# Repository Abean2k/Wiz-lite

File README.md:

# WizLite

A small, 2 player capable, ch552 based, game console with a 14x9 rgb led screen. 

## Design and Inspo:
I while back, I ordered some parts from LCSC, and as a part of that order I got a discounted CH552g chip. So, I wanted to find something cool and fun to do with it. My "solution", make a 'simple' two player game controller. 

In the process of building this, I made a number of decisions that made what was supposed to be a simple game controller into... an overengineered, ambitious project. For example, a simple OLED screen would have worked but did I do that, no. I wanted to make a small matrix of LEDS, which then became a matrix of rgb LEDS, which then finally became a tiny (807 size) 14x9 LED matrix. Additionally, the form factor of this whole project is VERY small (only around 75x50mm), making it even more interesting ;) 

## PCB:
For this project I made a two-layer PCB on Kicad, I limited myself to two layers in order to reduce the cost of the pcb manufacturing and to make it simpler. The pcb is lightly bigger than 75x50mm, and is designed with the LED matrix screen in the middle, the buttons on the top and bottom, Ch552 + passives to the right, and USB + passives to left. 

On the pcb, I added some text to demarcate the player one and player two sides, and I also added some pcb art to the front and back for *aesthetics*. 

### Schematic: 

### PCB Layout:

### Assembly/Ordering: 
The LED pads used on the pcb are technically over the "fine pitch" threshold of JLCPCB, and as such could be ordered with HASL. However, I recommend getting either OSP or ENIG as their pads are much flatter. When ordering, I would also make sure to order a stencil, as applying solder paste to the small led pads is very hard to do without applying excess solder. While soldering/reflowing, also make sure to not heat the leds too much (max 20 seconds at reflow tempurature).

You could also get the pcb assembled through something like JLCPCB PCBA service, however I chose not to for price saving reasons. 

## Firmware:
This project has the main firmware written in C, for the Arduino IDE, using the ch55xdunio library. Using C was new for me, but it was very similar to C++, and I was able to get a hang of it decently quickly. The basic idea is that the firmware drives the 9x14 RGB LED matrix, reads the user buttons, and executes game instructions. The firmware was (in my opinion) the hardest part of this project, but it also what I am most proud of. Anyway, here is the full breakdown of the code and other details about it.

#### Games (only one for now):
- Snake (single player)
- More TBD

Hold Player 1 LEFT + RIGHT for 2 seconds to leave a game and return to the menu.

#### How it works (like very high level) :
- **Menu:** A carousel of game cover pictures. LEFT/RIGHT pans, UP starts the selected game.
- **Screen:** screenUpdate(x, y, r, g, b) sets a pixel with (0,0) at the top left. It handles the split display, the zigzag LED wiring and a brightness limit so USB power limits aren't excided, and stores the result directly in the LED buffer. screenShow() sends that to the LEDs to acutally turn it on.
- **Pictures:** Each picture (like on the game cover carousel) has its own list of colors plus 14 rows of 9 characters. Use PictureMaker.html to draw one or import it from a Figma screenshot, and it writes the code for you. **NOTE:** This part (and only this part) of the code was made fully using AI, it looks vide coded, and that is because it is. Please understand if there are small bugs in it.
- **Text:** I added a 3x5 font (A-Z, 0-9) that can be called separately or with micro:bit style scrolling for longer texts.

#### Files:
| File | Purpose |
|---|---|
| `WizGameLite.ino` | Game menu and game list |
| `WizBase.c / .h` | Screen, buttons, text, shared pictures |
| `Snake.c / .h` | Snake game and its cover picture |
| `PictureMaker.html` | Tool for making pictures (opens in a browser, make sure javascript is enabled) |

#### PictureMaker:

#### Adding a game:
See the "HOW TO ADD A GAME" comment in `WizGameLite.ino`.

#### AI Usage: 
The code for the actual controller was fully coded by me (with only limited debug and learning help from AI). However, the online picture maker was fully vibe code, and it was also the first time I ever have vibe coded :)

## BOM: 
| Part | Designators | Quantity | Retailer | Total Price | Link |
|------|-------------|----------|----------|-------------|------|
| XL-0807RGBC-2812B-S (WS2812B-style addressable RGB LED, 2.0x1.8mm) `C41413181` | U2–U127 | 126x5 (640 ordered) | LCSC | $13.38 | [LCSC](https://www.lcsc.com/product-detail/C41413181.html) |
| 47uF ±10% 16V Ceramic Capacitor, 1210 (CS3225X7R476K160NRL) `C5440143` | C3, C4 | 2x5 | LCSC | $2.23 | [LCSC](https://www.lcsc.com/product-detail/C5440143.html) |
| 10kΩ ±1% 0805 Resistor (0805W8F1002T5E) `C17414` | R1–R4, R7–R11 | 9x5 (100 MOQ) | LCSC | $0.34 | [LCSC](https://www.lcsc.com/product-detail/C17414.html) |
| 100n Capacitor, 0805 | C1, C2 | 2x5 | Already have | $0.00 | [LCSC](https://www.lcsc.com/product-detail/C1711.html) |
| 330Ω Resistor, 0805 | R12, R13 | 2x5 | Already have | $0.00 | [LCSC](https://www.lcsc.com/product-detail/C17630.html) |
| 5.1kΩ Resistor, 0805 | R5, R6 | 2x5 | Already have | $0.00 | [LCSC](https://www.lcsc.com/product-detail/C27834.html) |
| CH552G Microcontroller (SOIC-16) | U1 | 1x5 | Already have | $0.00 | [LCSC](https://www.lcsc.com/product-detail/C111292.html) |
| USB-C Receptacle (HCTL HC-TYPE-C-16P-01A) | J1 | 1x5 | Already have | $0.00 | [LCSC](https://www.lcsc.com/product-detail/C2894897.html) |
| SMD Push Button Switch (TS-1088-xR020) | SW1–SW9 | 9x5 | Already have | $0.00 | [LCSC](https://www.lcsc.com/product-detail/C720477.html) |
| PCB (5x boards, Black, 1.6mm, OSP) | – | 1x5 | JLCPCB | $4.00 | – |
| SMT Stencil (75x100mm, no frame, top) | – | 1 | JLCPCB | $3.10 | – |
 
**Parts Subtotal:** LCSC ($15.95, after $1.15 discount) + JLCPCB ($7.10) = $23.05

**Shipping:** LCSC ($9.77) + JLCPCB ($11.83) = $21.60

**Total Cost For 5 PCBs: $44.65**

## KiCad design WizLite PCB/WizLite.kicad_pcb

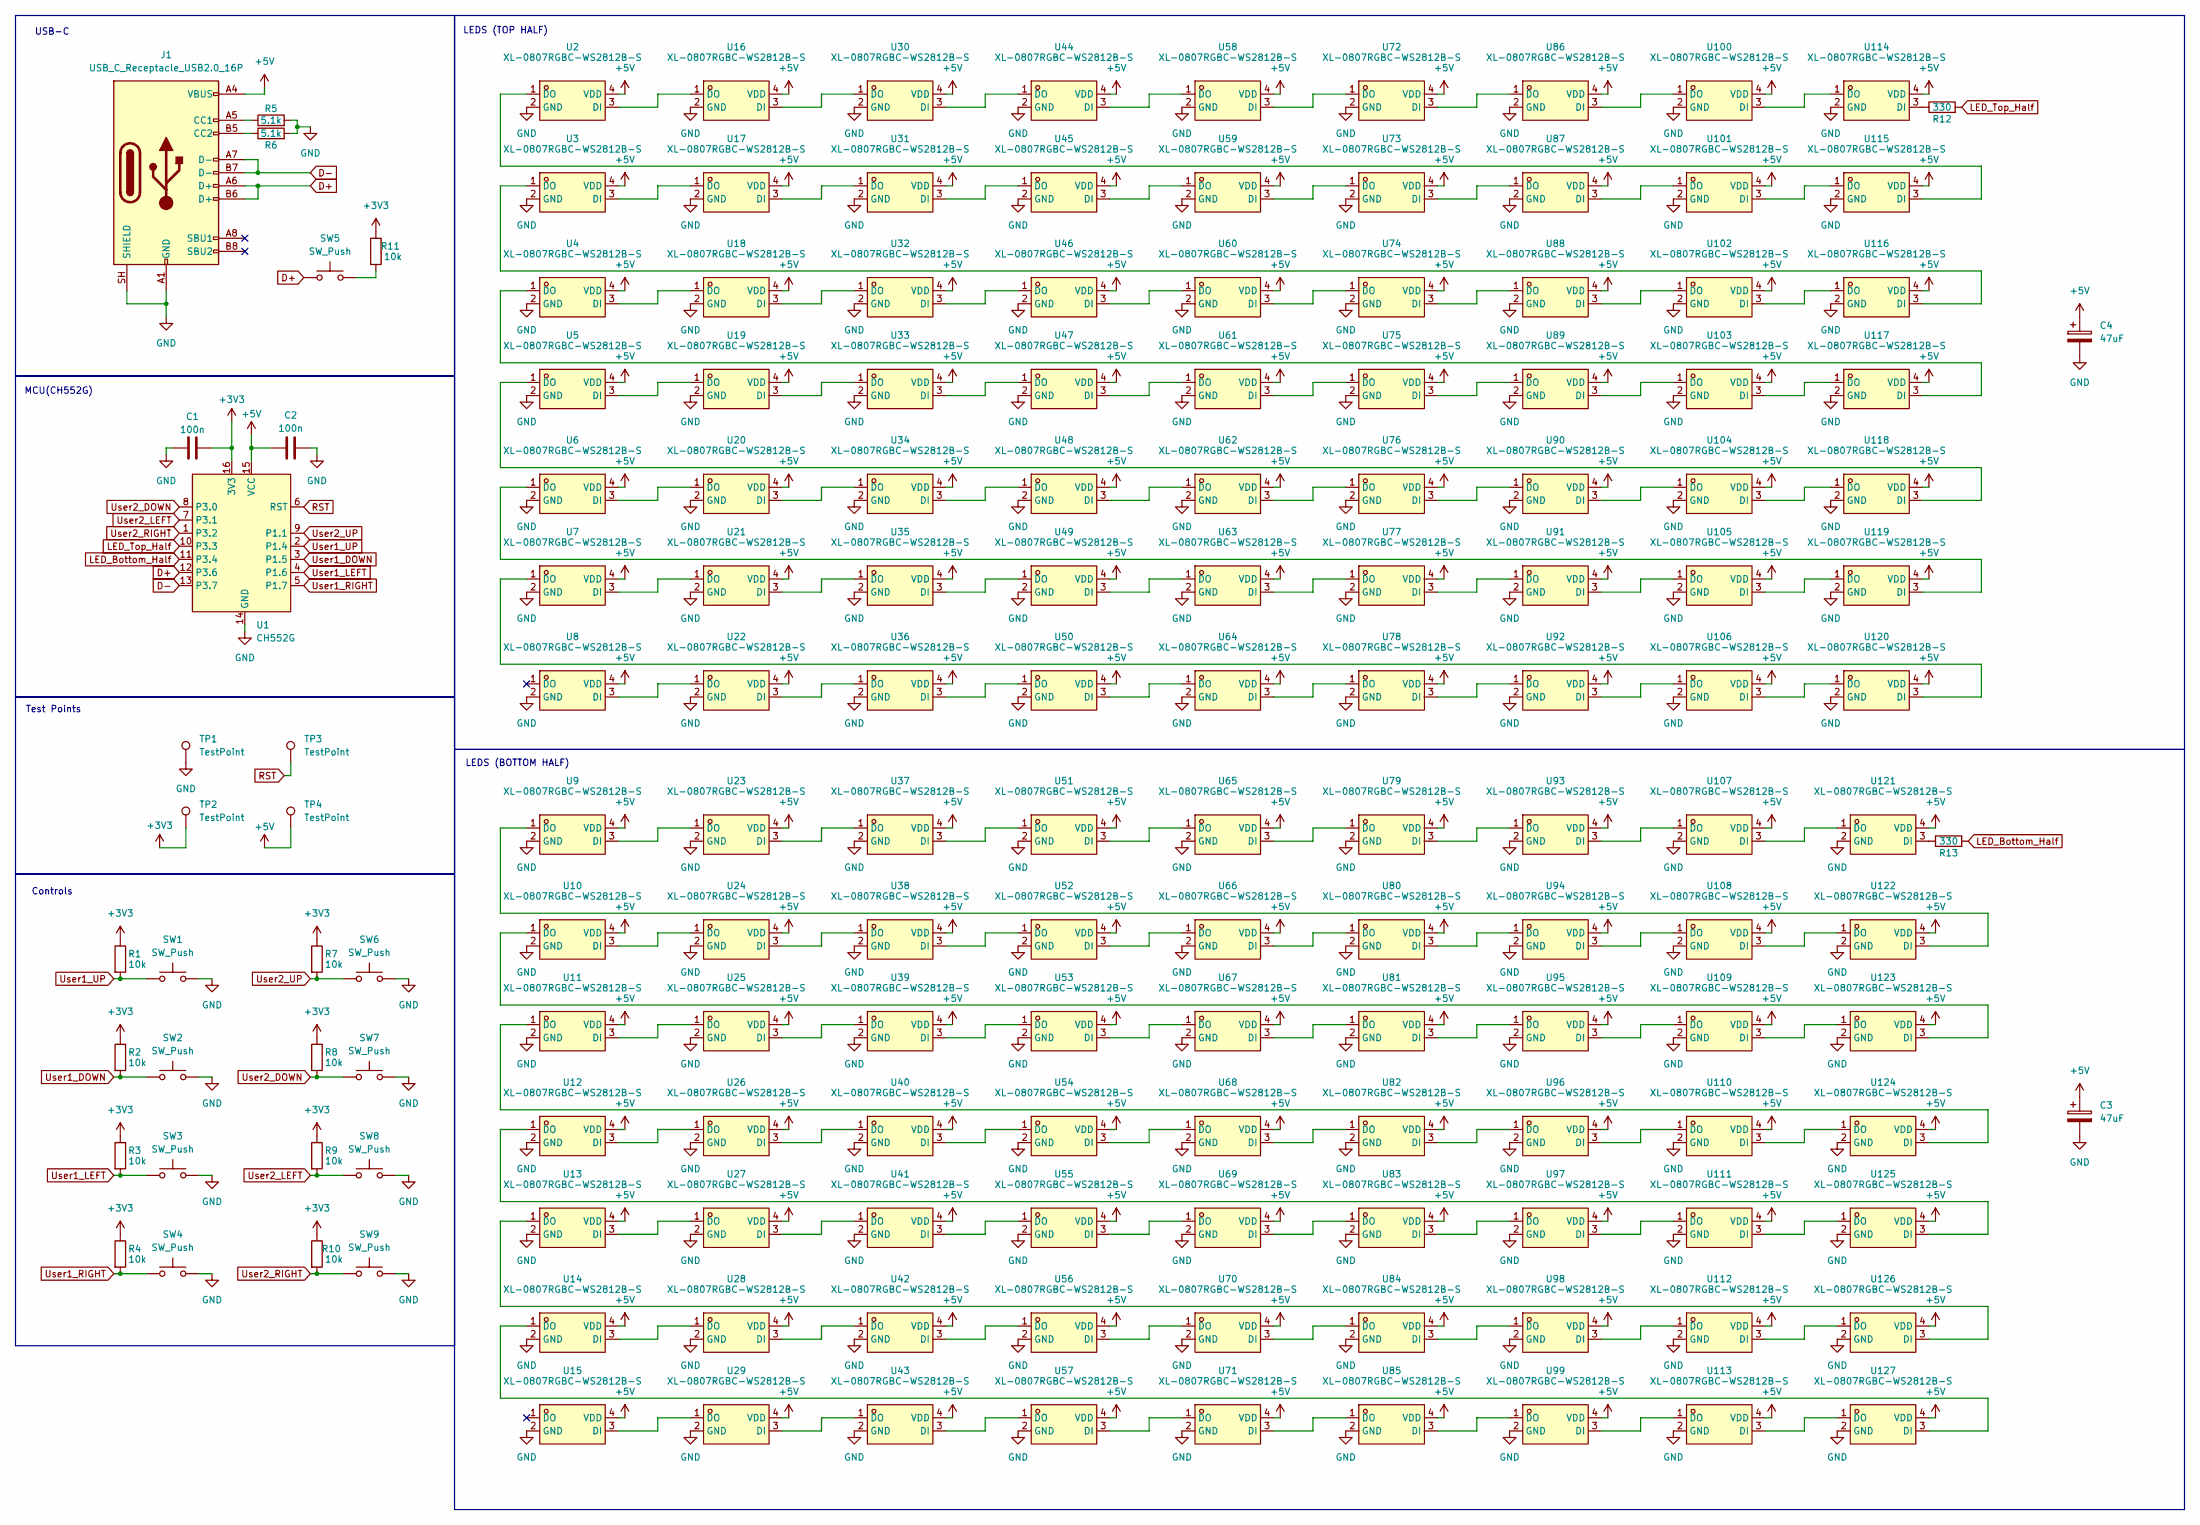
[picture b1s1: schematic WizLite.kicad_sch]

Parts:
C1, C2: 100n; C_0805_2012Metric_Pad1.18x1.45mm_HandSolder
C3, C4: 47uF; C_1210_3225Metric_Pad1.33x2.70mm_HandSolder
J1: USB_C_Receptacle_USB2.0_16P; USB_C_Receptacle_HCTL_HC-TYPE-C-16P-01A
R1, R2, R3, R4, R7, R8, R9, R10, R11: 10k; R_0805_2012Metric_Pad1.20x1.40mm_HandSolder
R5, R6: 5.1k; R_0805_2012Metric_Pad1.20x1.40mm_HandSolder
R12, R13: 330; R_0805_2012Metric_Pad1.20x1.40mm_HandSolder
SW1, SW2, SW3, SW4, SW5, SW6, SW7, SW8, SW9: SW_Push; SW_SPST_TS-1088-xR020
TP1, TP2, TP3, TP4: TestPoint; TestPoint_Pad_D1.0mm
U1: CH552G; SOIC-16_3.9x9.9mm_P1.27mm
U2, U3, U4, U5, U6, U7, U8, U9, U10, U11, U12, U13, U14, U15, U16, U17, U18, U19, U20, U21, U22, U23, U24, U25, U26, U27, U28, U29, U30, U31, U32, U33, U34, U35, U36, U37, U38, U39, U40, U41, U42, U43, U44, U45, U46, U47, U48, U49, U50, U51, U52, U53, U54, U55, U56, U57, U58, U59, U60, U61, U62, U63, U64, U65, U66, U67, U68, U69, U70, U71, U72, U73, U74, U75, U76, U77, U78, U79, U80, U81, U82, U83, U84, U85, U86, U87, U88, U89, U90, U91, U92, U93, U94, U95, U96, U97, U98, U99, U100, U101, U102, U103, U104, U105, U106, U107, U108, U109, U110, U111, U112, U113, U114, U115, U116, U117, U118, U119, U120, U121, U122, U123, U124, U125, U126, U127: XL-0807RGBC-WS2812B-S; LED-SMD_4P-L2.0-W1.8_XL-0807RGBC-WS2812B-S; MPN XL-0807RGBC-2812B-S; LCSC Part C41413181

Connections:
+3V3: C1.1, R1.1, R2.1, R3.1, R4.1, R7.1, R8.1, R9.1, R10.1, R11.1, TP2.1 (1_1), U1.16 (3V3)
+5V: C2.2, C3.1, C4.1, J1.A4 (VBUS), J1.A9 (VBUS), J1.B4 (VBUS), J1.B9 (VBUS), TP4.1 (1_1), U1.15 (VCC), U2.4 (VDD), U3.4 (VDD), U4.4 (VDD), U5.4 (VDD), U6.4 (VDD), U7.4 (VDD), U8.4 (VDD), U9.4 (VDD), U10.4 (VDD), U11.4 (VDD), U12.4 (VDD), U13.4 (VDD), U14.4 (VDD), U15.4 (VDD), U16.4 (VDD), U17.4 (VDD), U18.4 (VDD), U19.4 (VDD), U20.4 (VDD), U21.4 (VDD), U22.4 (VDD), U23.4 (VDD), U24.4 (VDD), U25.4 (VDD), U26.4 (VDD), U27.4 (VDD), U28.4 (VDD), U29.4 (VDD), U30.4 (VDD), U31.4 (VDD), U32.4 (VDD), U33.4 (VDD), U34.4 (VDD), U35.4 (VDD), U36.4 (VDD), U37.4 (VDD), U38.4 (VDD), U39.4 (VDD), U40.4 (VDD), U41.4 (VDD), U42.4 (VDD), U43.4 (VDD), U44.4 (VDD), U45.4 (VDD), U46.4 (VDD), U47.4 (VDD), U48.4 (VDD), U49.4 (VDD), U50.4 (VDD), U51.4 (VDD), U52.4 (VDD), U53.4 (VDD), U54.4 (VDD), U55.4 (VDD), U56.4 (VDD), U57.4 (VDD), U58.4 (VDD), U59.4 (VDD), U60.4 (VDD), U61.4 (VDD), U62.4 (VDD), U63.4 (VDD), U64.4 (VDD), U65.4 (VDD), U66.4 (VDD), U67.4 (VDD), U68.4 (VDD), U69.4 (VDD), U70.4 (VDD), U71.4 (VDD), U72.4 (VDD), U73.4 (VDD), U74.4 (VDD), U75.4 (VDD), U76.4 (VDD), U77.4 (VDD), U78.4 (VDD), U79.4 (VDD), U80.4 (VDD), U81.4 (VDD), U82.4 (VDD), U83.4 (VDD), U84.4 (VDD), U85.4 (VDD), U86.4 (VDD), U87.4 (VDD), U88.4 (VDD), U89.4 (VDD), U90.4 (VDD), U91.4 (VDD), U92.4 (VDD), U93.4 (VDD), U94.4 (VDD), U95.4 (VDD), U96.4 (VDD), U97.4 (VDD), U98.4 (VDD), U99.4 (VDD), U100.4 (VDD), U101.4 (VDD), U102.4 (VDD), U103.4 (VDD), U104.4 (VDD), U105.4 (VDD), U106.4 (VDD), U107.4 (VDD), U108.4 (VDD), U109.4 (VDD), U110.4 (VDD), U111.4 (VDD), U112.4 (VDD), U113.4 (VDD), U114.4 (VDD), U115.4 (VDD), U116.4 (VDD), U117.4 (VDD), U118.4 (VDD), U119.4 (VDD), U120.4 (VDD), U121.4 (VDD), U122.4 (VDD), U123.4 (VDD), U124.4 (VDD), U125.4 (VDD), U126.4 (VDD), U127.4 (VDD)
D+: J1.A6 (D+), J1.B6 (D+), SW5.1, U1.12 (P3.6)
D-: J1.A7 (D-), J1.B7 (D-), U1.13 (P3.7)
GND: C1.2, C2.1, C3.2, C4.2, J1.A1 (GND), J1.A12 (GND), J1.B1 (GND), J1.B12 (GND), J1.SH (SHIELD), R5.2, R6.2, SW1.2, SW2.2, SW3.2, SW4.2, SW6.2, SW7.2, SW8.2, SW9.2, TP1.1 (1_1), U1.14 (GND), U2.2 (GND), U3.2 (GND), U4.2 (GND), U5.2 (GND), U6.2 (GND), U7.2 (GND), U8.2 (GND), U9.2 (GND), U10.2 (GND), U11.2 (GND), U12.2 (GND), U13.2 (GND), U14.2 (GND), U15.2 (GND), U16.2 (GND), U17.2 (GND), U18.2 (GND), U19.2 (GND), U20.2 (GND), U21.2 (GND), U22.2 (GND), U23.2 (GND), U24.2 (GND), U25.2 (GND), U26.2 (GND), U27.2 (GND), U28.2 (GND), U29.2 (GND), U30.2 (GND), U31.2 (GND), U32.2 (GND), U33.2 (GND), U34.2 (GND), U35.2 (GND), U36.2 (GND), U37.2 (GND), U38.2 (GND), U39.2 (GND), U40.2 (GND), U41.2 (GND), U42.2 (GND), U43.2 (GND), U44.2 (GND), U45.2 (GND), U46.2 (GND), U47.2 (GND), U48.2 (GND), U49.2 (GND), U50.2 (GND), U51.2 (GND), U52.2 (GND), U53.2 (GND), U54.2 (GND), U55.2 (GND), U56.2 (GND), U57.2 (GND), U58.2 (GND), U59.2 (GND), U60.2 (GND), U61.2 (GND), U62.2 (GND), U63.2 (GND), U64.2 (GND), U65.2 (GND), U66.2 (GND), U67.2 (GND), U68.2 (GND), U69.2 (GND), U70.2 (GND), U71.2 (GND), U72.2 (GND), U73.2 (GND), U74.2 (GND), U75.2 (GND), U76.2 (GND), U77.2 (GND), U78.2 (GND), U79.2 (GND), U80.2 (GND), U81.2 (GND), U82.2 (GND), U83.2 (GND), U84.2 (GND), U85.2 (GND), U86.2 (GND), U87.2 (GND), U88.2 (GND), U89.2 (GND), U90.2 (GND), U91.2 (GND), U92.2 (GND), U93.2 (GND), U94.2 (GND), U95.2 (GND), U96.2 (GND), U97.2 (GND), U98.2 (GND), U99.2 (GND), U100.2 (GND), U101.2 (GND), U102.2 (GND), U103.2 (GND), U104.2 (GND), U105.2 (GND), U106.2 (GND), U107.2 (GND), U108.2 (GND), U109.2 (GND), U110.2 (GND), U111.2 (GND), U112.2 (GND), U113.2 (GND), U114.2 (GND), U115.2 (GND), U116.2 (GND), U117.2 (GND), U118.2 (GND), U119.2 (GND), U120.2 (GND), U121.2 (GND), U122.2 (GND), U123.2 (GND), U124.2 (GND), U125.2 (GND), U126.2 (GND), U127.2 (GND)
LED_Bottom_Half: R13.2, U1.11 (P3.4)
LED_Top_Half: R12.2, U1.10 (P3.3)
unnamed: J1.A5 (CC1), R5.1
unnamed: J1.B5 (CC2), R6.1
unnamed: R11.2, SW5.2
unnamed: U10.3 (DI), U24.1 (DO)
unnamed: U10.1 (DO), U123.3 (DI)
unnamed: U11.3 (DI), U25.1 (DO)
unnamed: U11.1 (DO), U124.3 (DI)
unnamed: U12.3 (DI), U26.1 (DO)
unnamed: U12.1 (DO), U125.3 (DI)
unnamed: U13.3 (DI), U27.1 (DO)
unnamed: U14.3 (DI), U28.1 (DO)
unnamed: U15.3 (DI), U29.1 (DO)
unnamed: U16.3 (DI), U30.1 (DO)
unnamed: U2.3 (DI), U16.1 (DO)
unnamed: U17.3 (DI), U31.1 (DO)
unnamed: U3.3 (DI), U17.1 (DO)
unnamed: U18.3 (DI), U32.1 (DO)
unnamed: U4.3 (DI), U18.1 (DO)
unnamed: U19.3 (DI), U33.1 (DO)
unnamed: U5.3 (DI), U19.1 (DO)
unnamed: U20.3 (DI), U34.1 (DO)
unnamed: U6.3 (DI), U20.1 (DO)
unnamed: U21.3 (DI), U35.1 (DO)
unnamed: U7.3 (DI), U21.1 (DO)
unnamed: U22.3 (DI), U36.1 (DO)
unnamed: U8.3 (DI), U22.1 (DO)
unnamed: U23.3 (DI), U37.1 (DO)
unnamed: U9.3 (DI), U23.1 (DO)
unnamed: U24.3 (DI), U38.1 (DO)
unnamed: U25.3 (DI), U39.1 (DO)
unnamed: U26.3 (DI), U40.1 (DO)
unnamed: U27.3 (DI), U41.1 (DO)
unnamed: U28.3 (DI), U42.1 (DO)
unnamed: U29.3 (DI), U43.1 (DO)
unnamed: U30.3 (DI), U44.1 (DO)
unnamed: U31.3 (DI), U45.1 (DO)
unnamed: U32.3 (DI), U46.1 (DO)
unnamed: U33.3 (DI), U47.1 (DO)
unnamed: U34.3 (DI), U48.1 (DO)
unnamed: U35.3 (DI), U49.1 (DO)
unnamed: U36.3 (DI), U50.1 (DO)
unnamed: U37.3 (DI), U51.1 (DO)
unnamed: U38.3 (DI), U52.1 (DO)
unnamed: U39.3 (DI), U53.1 (DO)
unnamed: U40.3 (DI), U54.1 (DO)
unnamed: U41.3 (DI), U55.1 (DO)
unnamed: U42.3 (DI), U56.1 (DO)
unnamed: U43.3 (DI), U57.1 (DO)
unnamed: U44.3 (DI), U58.1 (DO)
unnamed: U45.3 (DI), U59.1 (DO)
unnamed: U46.3 (DI), U60.1 (DO)
unnamed: U47.3 (DI), U61.1 (DO)
unnamed: U48.3 (DI), U62.1 (DO)
unnamed: U49.3 (DI), U63.1 (DO)
unnamed: U50.3 (DI), U64.1 (DO)
unnamed: U51.3 (DI), U65.1 (DO)
unnamed: U52.3 (DI), U66.1 (DO)
unnamed: U53.3 (DI), U67.1 (DO)
unnamed: U54.3 (DI), U68.1 (DO)
unnamed: U55.3 (DI), U69.1 (DO)
unnamed: U56.3 (DI), U70.1 (DO)
unnamed: U57.3 (DI), U71.1 (DO)
unnamed: U58.3 (DI), U72.1 (DO)
unnamed: U59.3 (DI), U73.1 (DO)
unnamed: U60.3 (DI), U74.1 (DO)
unnamed: U61.3 (DI), U75.1 (DO)
unnamed: U62.3 (DI), U76.1 (DO)
unnamed: U63.3 (DI), U77.1 (DO)
unnamed: U64.3 (DI), U78.1 (DO)
unnamed: U65.3 (DI), U79.1 (DO)
unnamed: U66.3 (DI), U80.1 (DO)
unnamed: U67.3 (DI), U81.1 (DO)
unnamed: U68.3 (DI), U82.1 (DO)
unnamed: U69.3 (DI), U83.1 (DO)
unnamed: U70.3 (DI), U84.1 (DO)
unnamed: U71.3 (DI), U85.1 (DO)
unnamed: U72.3 (DI), U86.1 (DO)
unnamed: U73.3 (DI), U87.1 (DO)
unnamed: U74.3 (DI), U88.1 (DO)
unnamed: U75.3 (DI), U89.1 (DO)
unnamed: U76.3 (DI), U90.1 (DO)
unnamed: U77.3 (DI), U91.1 (DO)
unnamed: U78.3 (DI), U92.1 (DO)
unnamed: U79.3 (DI), U93.1 (DO)
unnamed: U80.3 (DI), U94.1 (DO)
unnamed: U81.3 (DI), U95.1 (DO)
unnamed: U82.3 (DI), U96.1 (DO)
unnamed: U83.3 (DI), U97.1 (DO)
unnamed: U84.3 (DI), U98.1 (DO)
unnamed: U85.3 (DI), U99.1 (DO)
unnamed: U100.3 (DI), U114.1 (DO)
unnamed: U86.3 (DI), U100.1 (DO)
unnamed: U101.3 (DI), U115.1 (DO)
unnamed: U87.3 (DI), U101.1 (DO)
unnamed: U102.3 (DI), U116.1 (DO)
unnamed: U88.3 (DI), U102.1 (DO)
unnamed: U103.3 (DI), U117.1 (DO)
unnamed: U89.3 (DI), U103.1 (DO)
unnamed: U104.3 (DI), U118.1 (DO)
unnamed: U90.3 (DI), U104.1 (DO)
unnamed: U105.3 (DI), U119.1 (DO)
unnamed: U91.3 (DI), U105.1 (DO)
unnamed: U106.3 (DI), U120.1 (DO)
unnamed: U92.3 (DI), U106.1 (DO)
unnamed: U107.3 (DI), U121.1 (DO)
unnamed: U93.3 (DI), U107.1 (DO)
unnamed: U108.3 (DI), U122.1 (DO)
unnamed: U94.3 (DI), U108.1 (DO)
unnamed: U109.3 (DI), U123.1 (DO)
unnamed: U95.3 (DI), U109.1 (DO)
unnamed: U110.3 (DI), U124.1 (DO)
unnamed: U96.3 (DI), U110.1 (DO)
unnamed: U111.3 (DI), U125.1 (DO)
unnamed: U97.3 (DI), U111.1 (DO)
unnamed: U112.3 (DI), U126.1 (DO)
unnamed: U98.3 (DI), U112.1 (DO)
unnamed: U113.3 (DI), U127.1 (DO)
unnamed: U99.3 (DI), U113.1 (DO)
unnamed: R12.1, U114.3 (DI)
unnamed: U2.1 (DO), U115.3 (DI)
unnamed: U3.1 (DO), U116.3 (DI)
unnamed: U4.1 (DO), U117.3 (DI)
unnamed: U5.1 (DO), U118.3 (DI)
unnamed: U6.1 (DO), U119.3 (DI)
unnamed: U7.1 (DO), U120.3 (DI)
unnamed: R13.1, U121.3 (DI)
unnamed: U9.1 (DO), U122.3 (DI)
unnamed: U13.1 (DO), U126.3 (DI)
unnamed: U14.1 (DO), U127.3 (DI)
RST: TP3.1 (1_1), U1.6 (RST)
User1_DOWN: R2.2, SW2.1, U1.3 (P1.5)
User1_LEFT: R3.2, SW3.1, U1.4 (P1.6)
User1_RIGHT: R4.2, SW4.1, U1.5 (P1.7)
User1_UP: R1.2, SW1.1, U1.2 (P1.4)
User2_DOWN: R8.2, SW7.1, U1.8 (P3.0)
User2_LEFT: R9.2, SW8.1, U1.7 (P3.1)
User2_RIGHT: R10.2, SW9.1, U1.1 (P3.2)
User2_UP: R7.2, SW6.1, U1.9 (P1.1)

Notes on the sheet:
MCU(CH552G)
Controls
USB-C
LEDS (BOTTOM HALF)
Test Points
LEDS (TOP HALF)

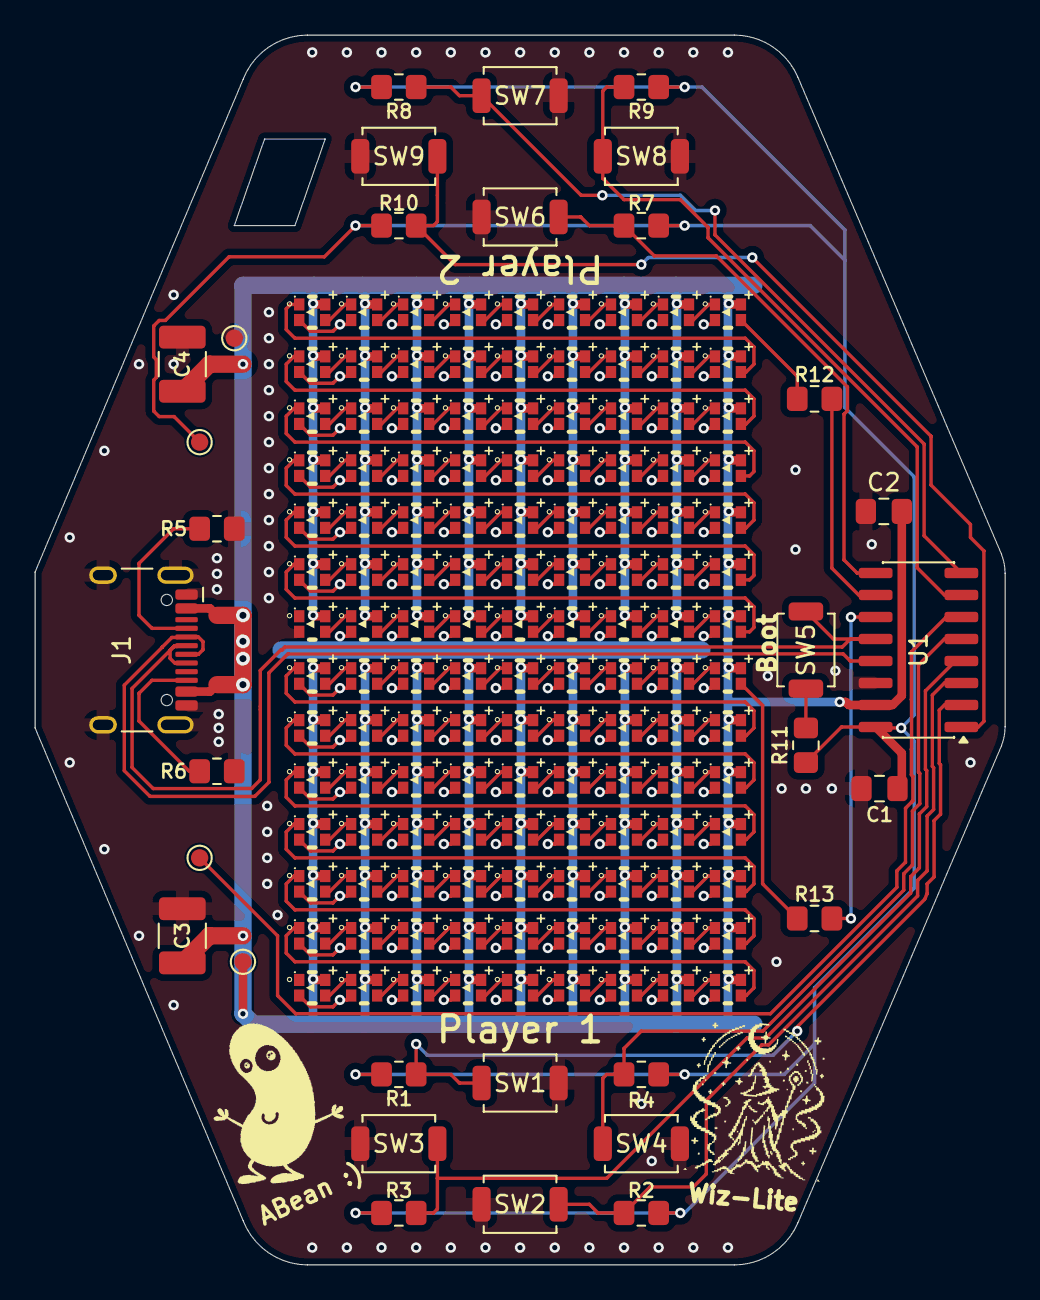
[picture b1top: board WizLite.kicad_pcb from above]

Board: 2 copper layers, 56.0 x 71.0 mm, 158 parts (0 on the bottom side), 145 nets.

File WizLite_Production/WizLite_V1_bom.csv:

Designator,Footprint,Quantity,Value,LCSC Part #
"C1, C2",0805,2,100n,
"C3, C4",1210,2,47uF,
J1,USB_C_Receptacle_HCTL_HC-TYPE-C-16P-01A,1,USB_C_Receptacle_USB2.0_16P,
"R1, R10, R11, R2, R3, R4, R7, R8, R9",0805,9,10k,
"R12, R13",0805,2,330,
"R5, R6",0805,2,5.1k,
"SW1, SW2, SW3, SW4, SW5, SW6, SW7, SW8, SW9",SW_SPST_TS-1088-xR020,9,SW_Push,
"TP1, TP2, TP3, TP4",TestPoint_Pad_D1.0mm,4,TestPoint,
U1,SOIC-16_3.9x9.9mm_P1.27mm,1,CH552G,
"U10, U100, U101, U102, U103, U104, U105, U106, U107, U108, U109, U11, U110, U111, U112, U113, U114, U115, U116, U117, U118, U119, U12, U120, U121, U122, U123, U124, U125, U126, U127, U13, U14, U15, U16, U17, U18, U19, U2, U20, U21, U22, U23, U24, U25, U26, U27, U28, U29, U3, U30, U31, U32, U33, U34, U35, U36, U37, U38, U39, U4, U40, U41, U42, U43, U44, U45, U46, U47, U48, U49, U5, U50, U51, U52, U53, U54, U55, U56, U57, U58, U59, U6, U60, U61, U62, U63, U64, U65, U66, U67, U68, U69, U7, U70, U71, U72, U73, U74, U75, U76, U77, U78, U79, U8, U80, U81, U82, U83, U84, U85, U86, U87, U88, U89, U9, U90, U91, U92, U93, U94, U95, U96, U97, U98, U99",LED-SMD_4P-L2.0-W1.8_XL-0807RGBC-WS2812B-S,126,XL-0807RGBC-WS2812B-S,C41413181
